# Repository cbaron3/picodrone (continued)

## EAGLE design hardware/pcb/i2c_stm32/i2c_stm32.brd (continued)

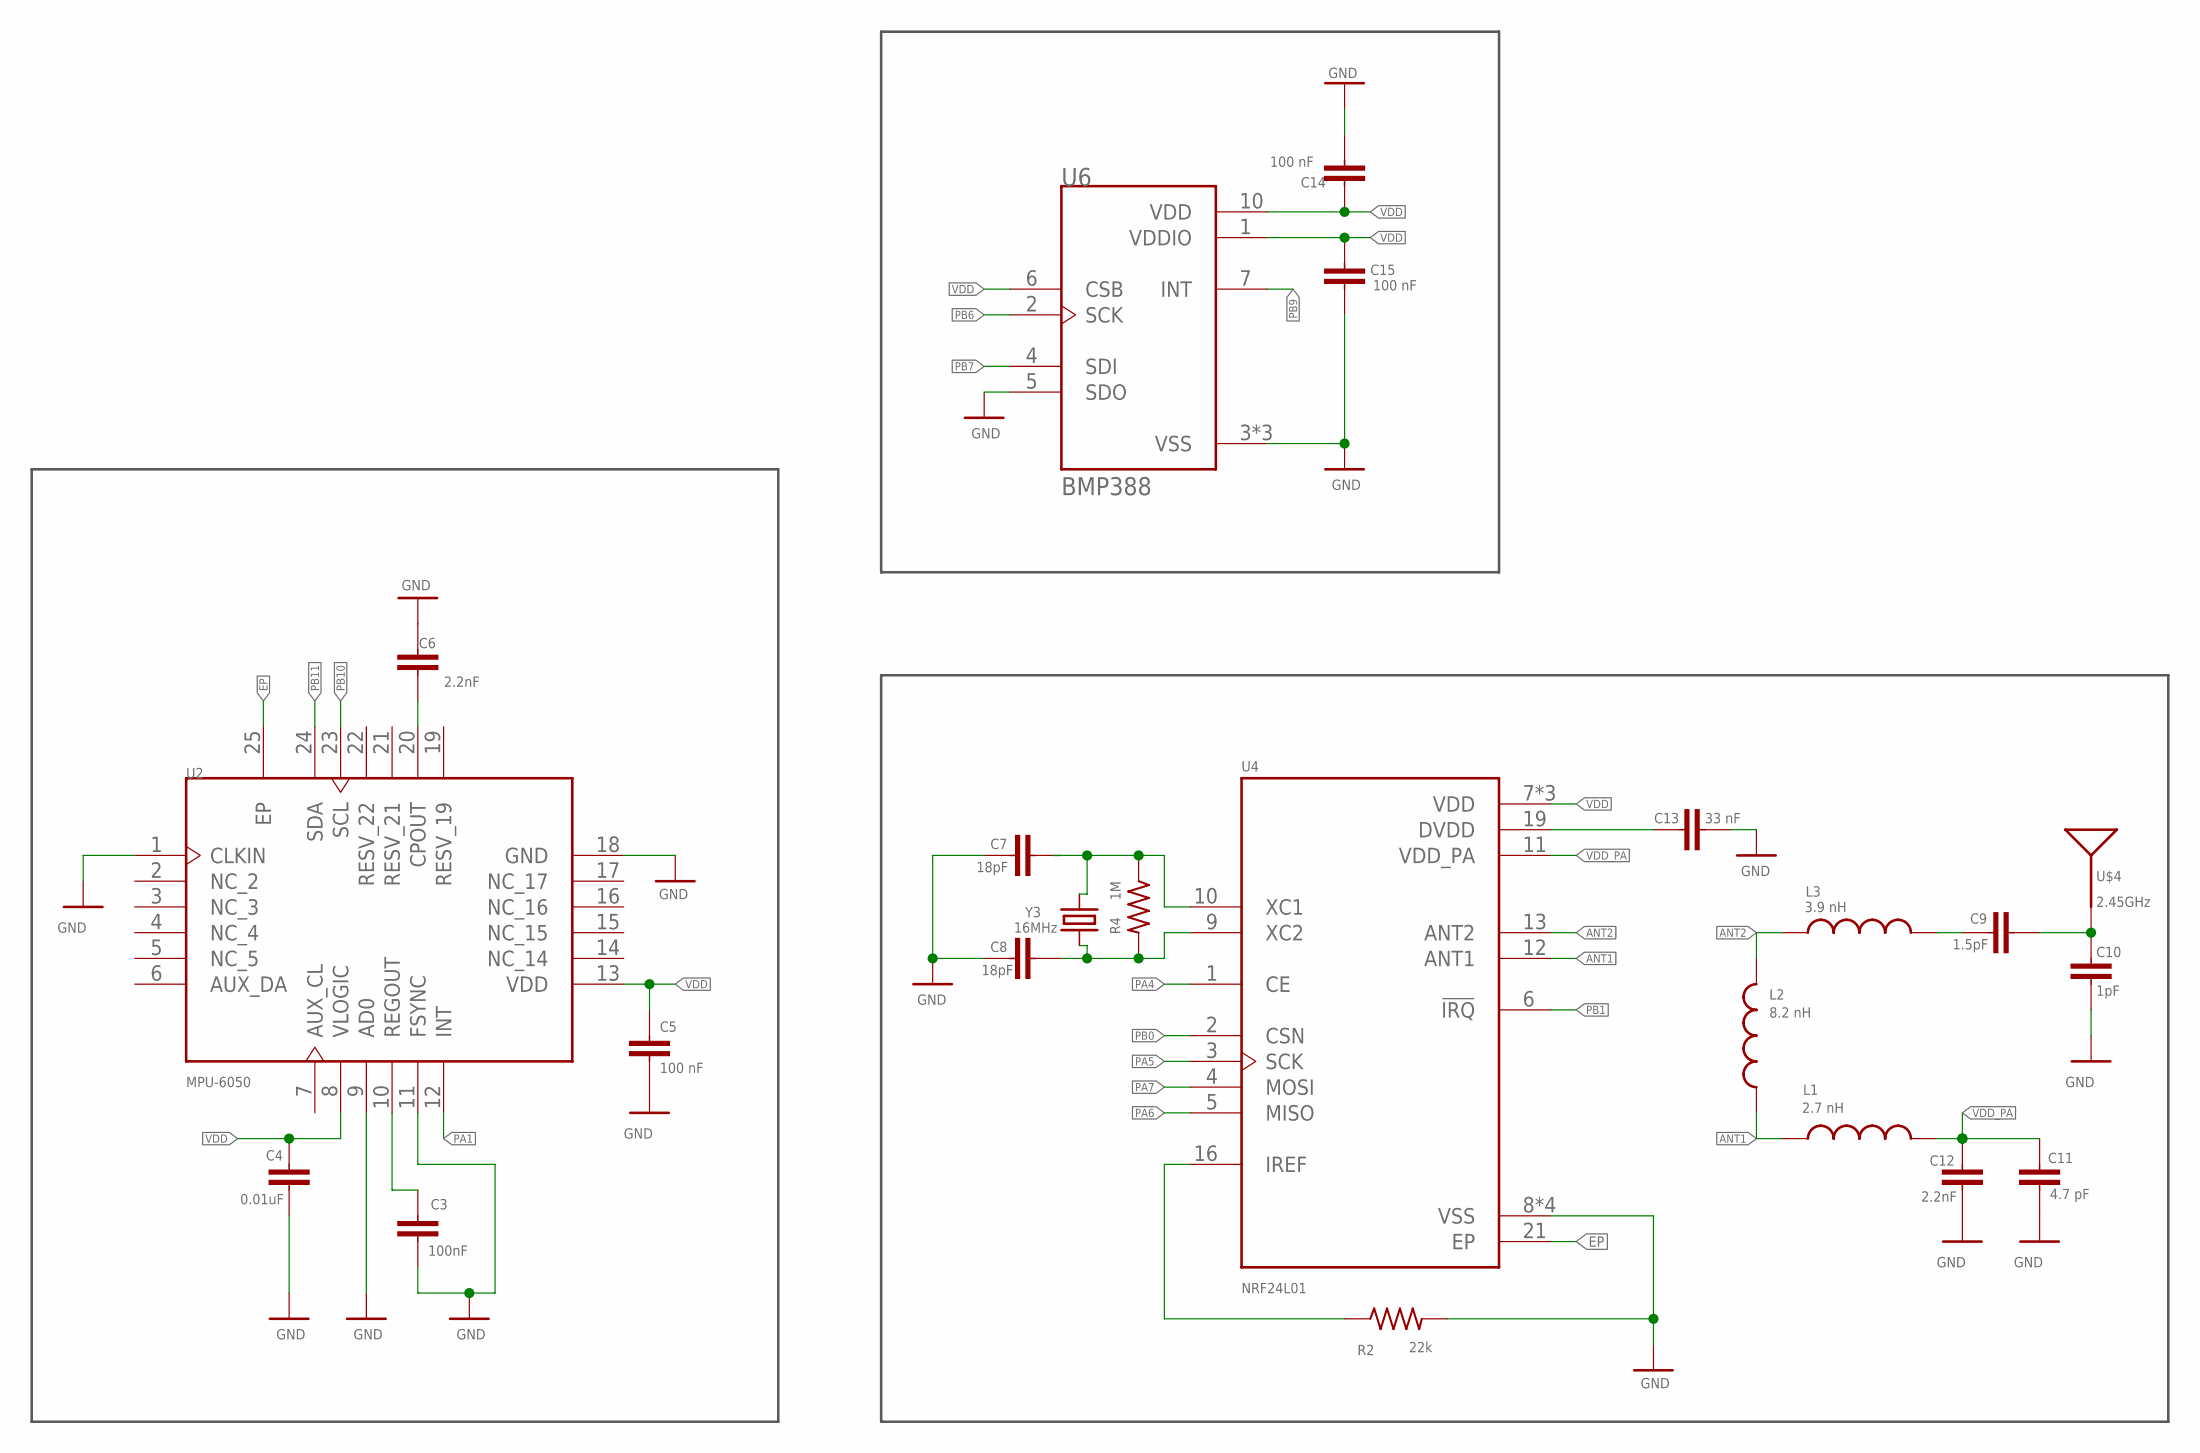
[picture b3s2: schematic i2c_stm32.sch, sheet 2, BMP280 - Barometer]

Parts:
C3: 100nF; CAP_0603
C4: 0.01uF; CAP_0603
C5, C14, C15: 100 nF; CAP_0603
C6, C12: 2.2nF; CAP_0603
C7, C8: 18pF; CAP_0603
C9: 1.5pF; CAP_0603
C10: 1pF; CAP_0603
C11: 4.7 pF; CAP_0603
C13: 33 nF; CAP_0603
L1: 2.7 nH; RESC0603_M
L2: 8.2 nH; RESC0603_M
L3: 3.9 nH; RESC0603_M
R2: 22k; RES_0603
R4: 1M; RES_0603
U2: MPU-6050; 24-VFQFN
U4: NRF24L01; QFN50P400X400X95-21N
U6: BMP388; PQFN50P200X200X80-10N
U$4: 2.45GHz; ANT-2.4GHZ-6.5X2.2MM
Y3: 16MHz; CRYSTAL-SMD-5X3.2-4PAD

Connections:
ANT1: L1.1, L2.1, U4.12 (ANT1)
ANT2: L2.2, L3.1, U4.13 (ANT2)
EP: U2.25 (EP), U4.21 (EP)
GND: C3.2, C4.2, C5.2, C6.2, C7.2, C8.2, C10.1, C11.1, C12.1, C13.2, C14.2, C15.1, R2.2, U2.1 (CLKIN), U2.9 (AD0), U2.11 (FSYNC), U2.18 (GND), U4.8 (VSS), U4.14 (VSS), U4.17 (VSS), U4.20 (VSS), U6.3 (VSS), U6.5 (SDO), U6.8 (VSS), U6.9 (VSS); also elsewhere on the board
unnamed: C3.1, U2.10 (REGOUT)
unnamed: C6.1, U2.20 (CPOUT)
unnamed: C8.1, R4.2, U4.9 (XC2), Y3.1
unnamed: C7.1, R4.1, U4.10 (XC1), Y3.3 (2)
unnamed: R2.1, U4.16 (IREF)
unnamed: C9.2, C10.2, U$4.FEED
unnamed: C9.1, L3.2
unnamed: C13.1, U4.19 (DVDD)
PA1: U2.12 (INT); also elsewhere on the board
PA4: U4.1 (CE); also elsewhere on the board
PA5: U4.3 (SCK); also elsewhere on the board
PA6: U4.5 (MISO); also elsewhere on the board
PA7: U4.4 (MOSI); also elsewhere on the board
PB0: U4.2 (CSN); also elsewhere on the board
PB1: U4.6 (!IRQ); also elsewhere on the board
PB6: U6.2 (SCK); also elsewhere on the board
PB7: U6.4 (SDI); also elsewhere on the board
PB9: U6.7 (INT); also elsewhere on the board
PB10: U2.23 (SCL); also elsewhere on the board
PB11: U2.24 (SDA); also elsewhere on the board
VDD: C4.1, C5.1, C14.1, C15.2, U2.8 (VLOGIC), U2.13 (VDD), U4.7 (VDD), U4.15 (VDD), U4.18 (VDD), U6.1 (VDDIO), U6.6 (CSB), U6.10 (VDD); also elsewhere on the board
VDD_PA: C11.2, C12.2, L1.2, U4.11 (VDD_PA)

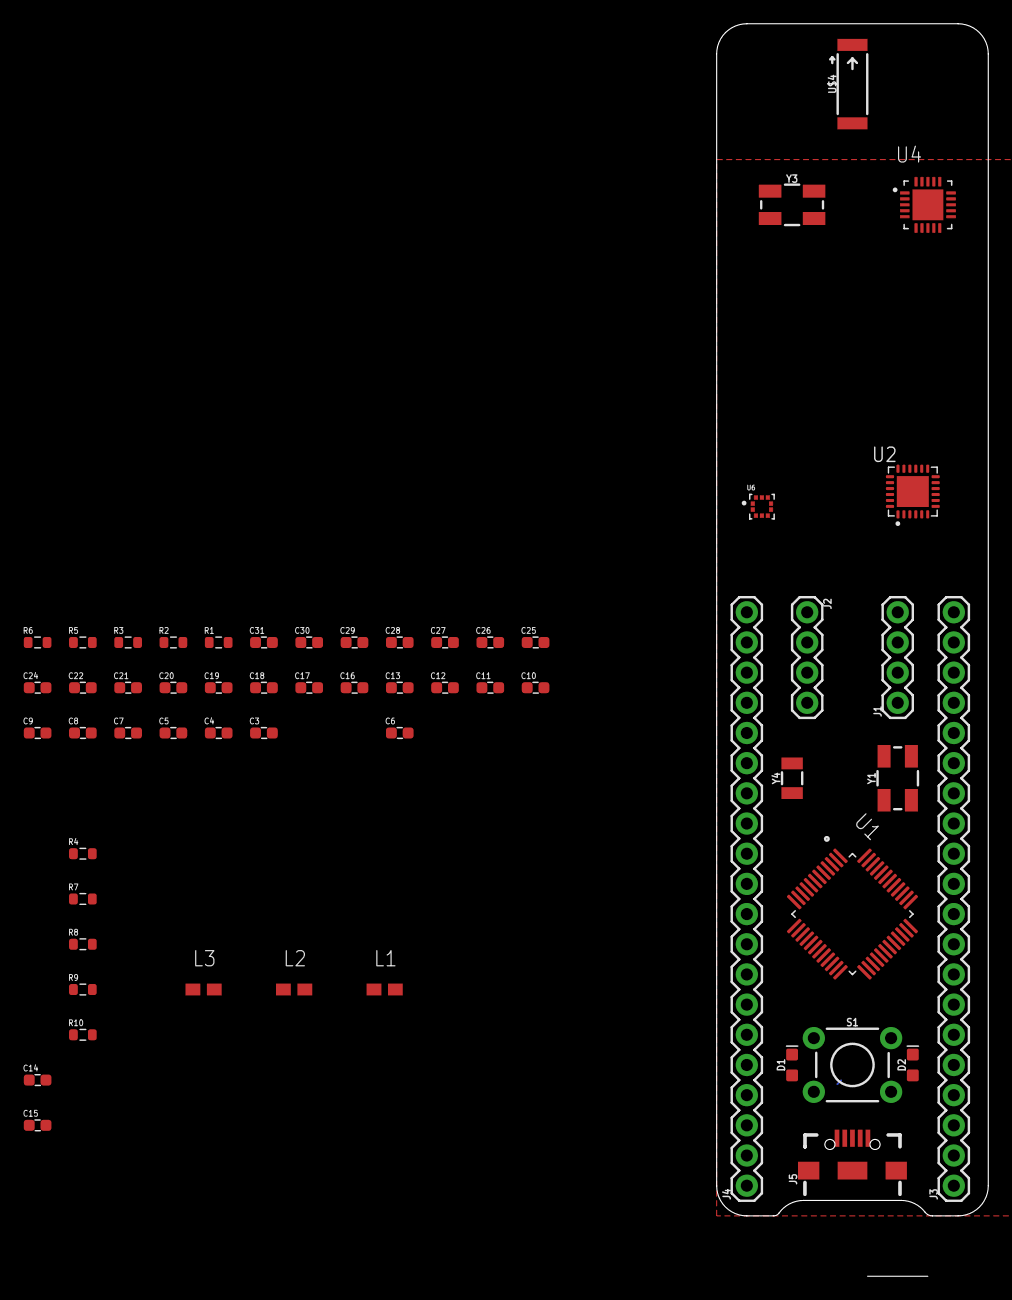
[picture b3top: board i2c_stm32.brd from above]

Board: 2 copper layers, 22.9 x 105.4 mm, 58 parts (1 on the bottom side), 54 nets.

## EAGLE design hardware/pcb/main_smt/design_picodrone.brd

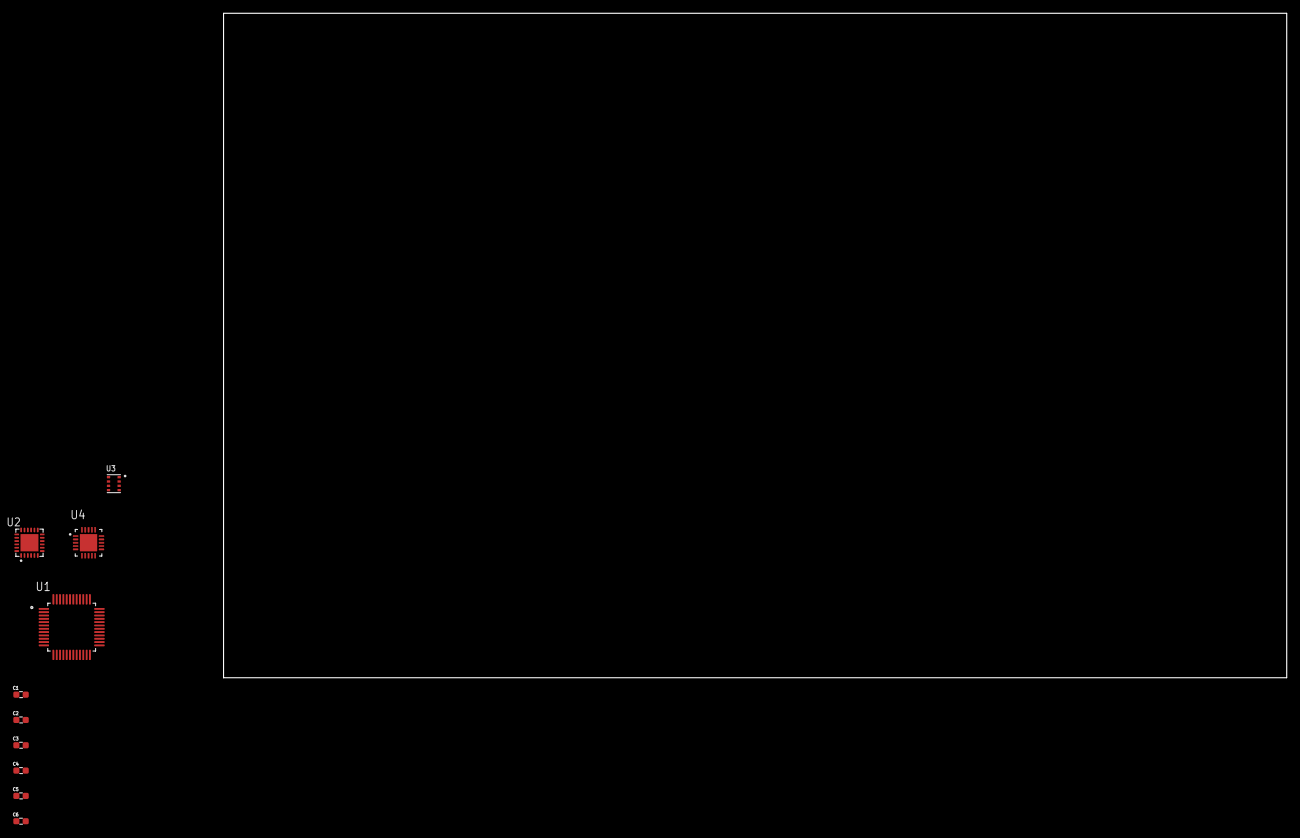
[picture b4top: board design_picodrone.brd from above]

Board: 2 copper layers, 160.0 x 100.0 mm, 10 parts (0 on the bottom side), 9 nets, no tracks yet.

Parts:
C1, C2, C5: 100 nF; CAP_0603
C3: 0.1 uF; CAP_0603
C4: 0.01 uF; CAP_0603
C6: 2200 pF; CAP_0603
U1: STM32F103C8T6; QFP50P900X900X160-48N
U2: MPU-6050; 24-VFQFN
U3: BMP280; XDCR_BMP280
U4: NRF24L01; QFN50P400X400X95-21N

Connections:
EP: U2.25, U4.21
GND: C1.1, C2.2, C3.2, C4.2, C5.2, C6.2, U2.1, U2.9, U2.11, U2.18, U3.1, U3.5, U3.7
unnamed: C4.1, U2.8
unnamed: C3.1, U2.10
unnamed: C6.1, U2.20
SDA: U2.24, U3.3
VDD: C1.2, C5.1, U1.24, U1.36, U1.48, U2.13, U3.8, U4.7, U4.15, U4.18
VDDIO: C2.1, U3.2, U3.6
VSS: U1.23, U1.35, U1.47, U4.8, U4.14, U4.17, U4.20

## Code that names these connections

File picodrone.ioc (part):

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Mcu.Name=STM32F103C(8-B)Tx
Mcu.Package=LQFP48
Mcu.UserName=STM32F103C8Tx
PA10.Mode=Asynchronous
PA10.Signal=USART1_RX
PA13.Mode=JTAG_4_pins
PA13.Signal=SYS_JTMS-SWDIO
PA14.Mode=JTAG_4_pins
PA14.Signal=SYS_JTCK-SWCLK
PA15.Mode=JTAG_4_pins
PA15.Signal=SYS_JTDI
PA5.Mode=Full_Duplex_Master
PA5.Signal=SPI1_SCK
PA6.Mode=Full_Duplex_Master
PA6.Signal=SPI1_MISO
PA7.Mode=Full_Duplex_Master
PA7.Signal=SPI1_MOSI
PA9.Mode=Asynchronous
PA9.Signal=USART1_TX
PB0.Signal=GPIO_Output
PB1.Signal=GPIO_Output
PB3.Mode=JTAG_4_pins
PB3.Signal=SYS_JTDO-TRACESWO
PC13-TAMPER-RTC.Signal=GPIO_Output
PD0-OSC_IN.Mode=HSE-External-Oscillator
PD0-OSC_IN.Signal=RCC_OSC_IN
PD1-OSC_OUT.Mode=HSE-External-Oscillator
PD1-OSC_OUT.Signal=RCC_OSC_OUT
RCC.SYSCLKFreq_VALUE=72000000
RCC.SYSCLKSource=RCC_SYSCLKSOURCE_PLLCLK
board=custom

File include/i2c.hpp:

#ifndef INCLUDE_IMU_H
#define INCLUDE_IMU_H

#include "stm32f1xx_hal.h"
#include "stm32f1xx.h"
#include "utility.hpp"

namespace picodrone
{

namespace i2c
{
    I2C_HandleTypeDef m_I2C1;
    I2C_HandleTypeDef m_I2C2;

    void init() {
        // I2C1 -> SDA on PB7, SCL on PB6
        // I2C2 -> SDA on PB11, SCL on PB10
        __HAL_RCC_I2C1_CLK_ENABLE();
        __HAL_RCC_I2C2_CLK_ENABLE();
        __HAL_RCC_GPIOB_CLK_ENABLE();

        GPIO_InitTypeDef  GPIO_InitStruct;

        // I2C1 SCL
        GPIO_InitStruct.Pin       = GPIO_PIN_6;
        GPIO_InitStruct.Mode      = GPIO_MODE_AF_OD;
        GPIO_InitStruct.Pull      = GPIO_PULLUP;
        GPIO_InitStruct.Speed     = GPIO_SPEED_FREQ_HIGH;
        HAL_GPIO_Init(GPIOB, &GPIO_InitStruct);
            
        // I2C1 SDA
        GPIO_InitStruct.Pin       = GPIO_PIN_7;
        HAL_GPIO_Init(GPIOB, &GPIO_InitStruct);

        // I2C2 SCL
        GPIO_InitStruct.Pin       = GPIO_PIN_10;
        HAL_GPIO_Init(GPIOB, &GPIO_InitStruct);

        // I2C2 SDA
        GPIO_InitStruct.Pin       = GPIO_PIN_11;
        HAL_GPIO_Init(GPIOB, &GPIO_InitStruct);

        // IMU1 instance for the BMP280
        m_I2C1.Instance             = I2C1;
        m_I2C1.Init.ClockSpeed      = 100000; // 100 kHz
        m_I2C1.Init.DutyCycle       = I2C_DUTYCYCLE_2;
        m_I2C1.Init.OwnAddress1     = 0x00;  // Either 076 or 077
        m_I2C1.Init.AddressingMode  = I2C_ADDRESSINGMODE_7BIT;
        m_I2C1.Init.DualAddressMode = I2C_DUALADDRESS_DISABLE;
        m_I2C1.Init.OwnAddress2     = 0xFF;
        m_I2C1.Init.GeneralCallMode = I2C_GENERALCALL_DISABLE;
        m_I2C1.Init.NoStretchMode   = I2C_NOSTRETCH_DISABLE;  

        if(HAL_I2C_Init(&m_I2C1) != HAL_OK)
        {
            /* Initialization Error */
            lib::util::ErrorHandler(__FILE__, __LINE__);
        }

        // IMU2 instance for the MPU6050
    }
}

}

#endif // INCLUDE_IMU_H

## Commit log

2020-10-27 Initial project structure
2020-10-28 Startup script + linker file complete. Tested in other project with STM32 dependencies linked
2020-11-01 blink and basic pwm code working
2020-11-01 confirmed using cpp works in current build system
2020-11-03 interface refactor & add FreeRTOS to build system
2020-11-05 cpp freertos added
2020-11-05 dependency cleanup
2020-11-05 more dependency cleanup
2020-11-05 finalized dependency clean up
2020-11-05 reverted back to C interface; think it is much much cleaner
2020-11-05 adding uart
2020-11-05 freertos tasks setusp
2020-11-06 USART1 confirmed working with oscilloscope
2020-11-06 Reduced flash usage by 30k (~50%) by changing from HAL_TIM to LL_TIM
2020-11-07 more memory size debugging
2020-11-07 Basic xQueue send/receive w/ FreeRTOS
2020-11-08 Basic I2C working with BMP180, heavy refactor needed
2020-11-09 attempt to create cleaner interface, code left commented out cause won't compile
2020-11-13 code abstraction work, temp
2020-11-13 basic hardware setup
2020-11-15 completed mosfet test pcb used for testing V, I characteristics of different sot23 fets
2020-11-19 pcb work
2020-11-21 board renaming
2020-11-26 added nrf24 smt to i2c test board
2020-11-27 Schematic finalized (besides crystal load c ap and resistor values)
2020-11-27 schematic updates
2020-11-28 Replaced BMP280 w/ BMP388 cause of stock availability and another tweaks to schematic
2020-11-29 Schematic finished, BOM verified
2020-11-29 finalized circuit boards and ordered w/ gerber files
2020-12-04 minor cleanup
2020-12-07 started file restructure, trying to get new task base working
2020-12-11 Finished restructure, just need to split common into H and C files or inline/static all functions/variables
2020-12-11 Trying to get lib components working, at least got queue to be passed in as param
2020-12-12 Completed restructure with tasks in individual projects
2020-12-13 Working on cleaner interface, UART working with LL now
2020-12-13 i2c not working now
2020-12-13 magically fixed the i2c issue by moving init to task scope instead of main scope
2020-12-14 MPU working, SPI next
2020-12-14 Validated NRF24 connection by configuring settings correctly. Had to use library to make it easy
2020-12-15 Some more validation
2020-12-28 NRF test, that failed
2021-02-28 updated board design
2021-02-28 Include mini NRF24 library
2021-03-07 Updated 4-layer design with NRF24 module instead of actual chip
2021-03-10 Stripped old code for fresh start
2021-03-13 Started refactor on controller
2021-03-19 Simple dockerfile with script that allows for basic build process
2021-03-20 Added clean build to build script
2021-03-20 Added python script functionality
2021-03-20 Added elf size tracking to build process with persistent memory
2021-03-21 Script clean up
2021-03-21 Completed elf size tracking using python script for both transmitter and drone
2021-03-21 Included dockerfile for hardware file auto-generation (images)
2021-03-24 Build process refined
2021-05-19 controller init refactor using C instead of C++ interface. works with v3 board
2021-05-20 UART confirmed working on v3
2021-05-20 pushing v3 board to repo
2022-05-16 Start from scratch, already proved can now get NRF24 working with STM32
